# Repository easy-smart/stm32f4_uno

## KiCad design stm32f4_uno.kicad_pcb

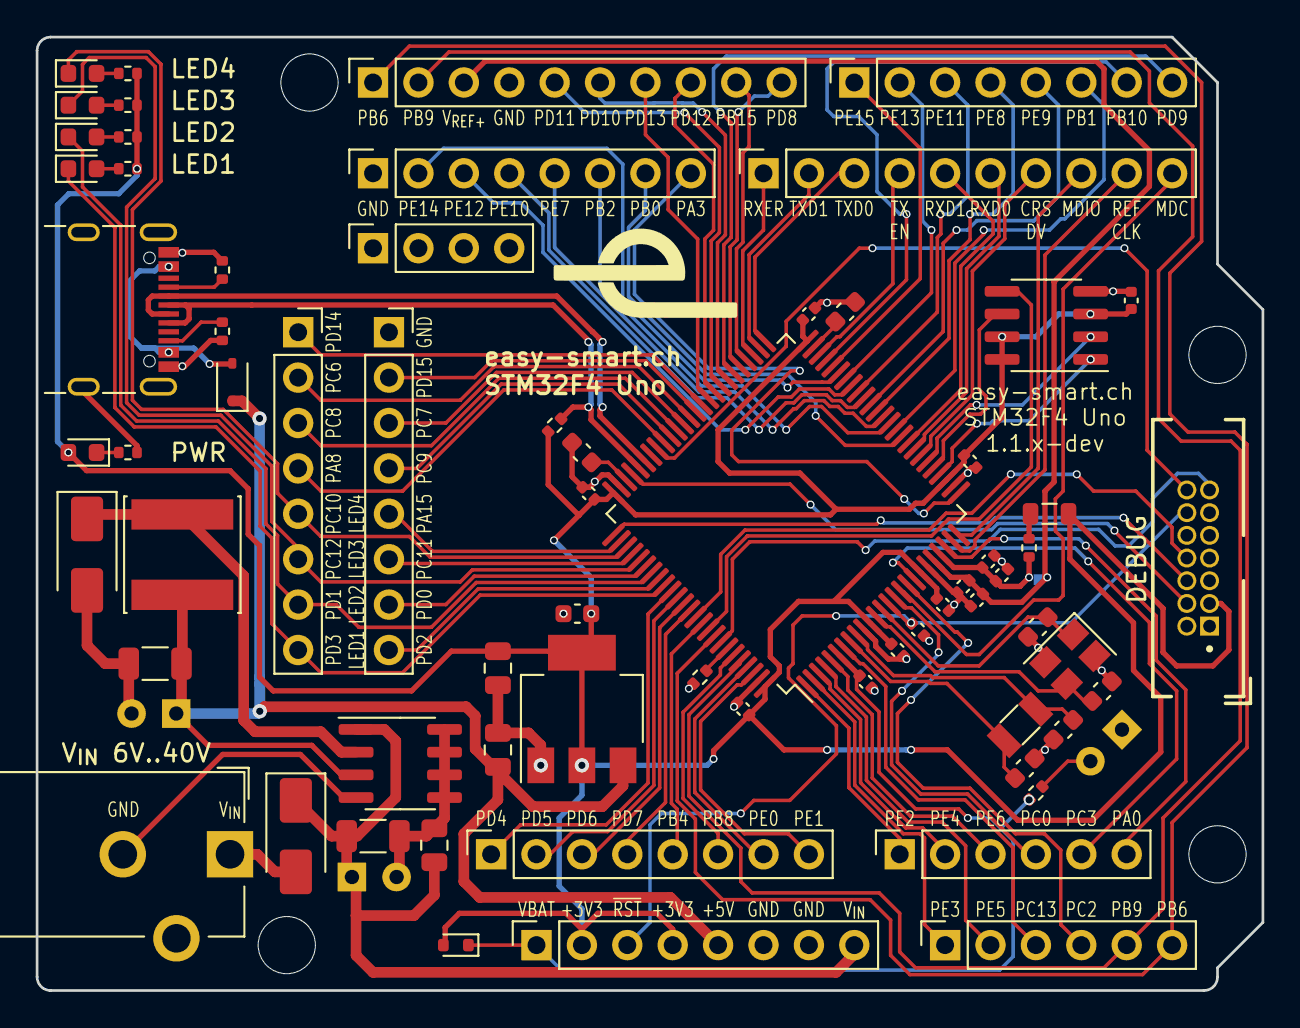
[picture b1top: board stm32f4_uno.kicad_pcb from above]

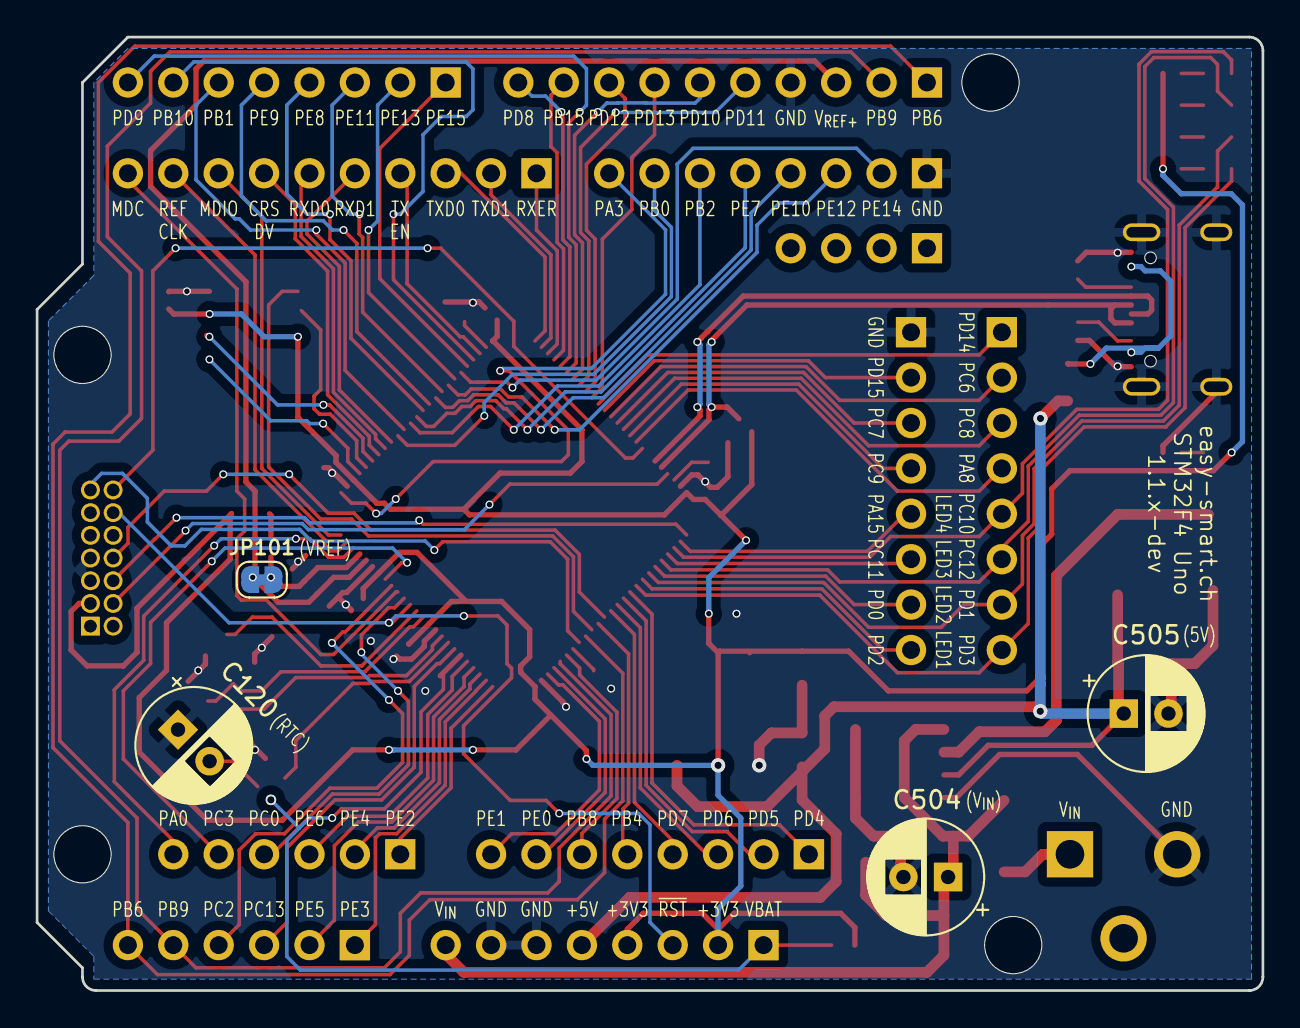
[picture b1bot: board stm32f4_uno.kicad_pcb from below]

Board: 2 copper layers, 68.6 x 53.3 mm, 75 parts (4 on the bottom side), 104 nets.

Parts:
C101: 4u7 16V; C_0603_1608Metric
C102, C103, C104, C105, C106, C107, C108, C110: 100n; C_0402_1005Metric
C109, C111, C112: 1u; C_0402_1005Metric
C113, C301: 100n 16V; C_0402_1005Metric
C114, C115: 30p 50V; C_0603_1608Metric
C116, C117: 2u2 16V; C_0603_1608Metric
C118, C119: 8p2 50V; C_0603_1608Metric
C120, C504, C505: ?; CP_Radial_D6.3mm_P2.50mm
C401, C402: 22u 25V; C_0805_2012Metric
C501: 1u 50V; C_0805_2012Metric
C502: 10u 50V; C_1206_3216Metric
C503: 47uF 10V; C_1206_3216Metric
D101: LED green; LED_0603_1608Metric
D102: LED yellow; LED_0603_1608Metric
D103: LED red; LED_0603_1608Metric
D104: LED blue; LED_0603_1608Metric
D105: 1N5819WS; D_SOD-323
D106: SS210; D_SMA
D107: 1N4148WT; D_SOD-523
D401: LED green (PWR); LED_0603_1608Metric
D501: SS34; D_SMA
J1: Conn_ST_STDC14; Amphenol ICC 20021511-00014T4LF
J101, J103, J104, J105: STM32 GPIO; PinSocket_1x08_P2.54mm_Vertical
J102: Digital/PWM; PinSocket_1x10_P2.54mm_Vertical
J106: Power; PinSocket_1x08_P2.54mm_Vertical
J107: Ethernet; PinSocket_1x10_P2.54mm_Vertical
J108: STM32 GPIO; PinSocket_1x06_P2.54mm_Vertical
J109: Digital/PWM; PinSocket_1x08_P2.54mm_Vertical
J110: Analog; PinSocket_1x06_P2.54mm_Vertical
J111: Conn_01x04; PinSocket_1x04_P2.54mm_Vertical
J112: Barrel_Jack; CUI Devices PJ-102AH.pdf
J201: SHOU HAN TYPE-C 16PIN 2MD(073) (C2765186); SHOU HAN TYPE-C 16PIN 2MD(073)
JP101: Jumper_2_Bridged; SolderJumper-2_P1.3mm_Bridged_RoundedPad1.0x1.5mm
L101: 600Ω@100MHz; L_0805_2012Metric
L501: 68uH 1A; L_Sunlord_SWPA6045S
MH1, MH2, MH3, MH4: MountingHole_3.2mm
R101: 47; R_0402_1005Metric
R102: 10k; R_0402_1005Metric
R103, R401: 200; R_0402_1005Metric
R104, R105: 330; R_0402_1005Metric
R106: 150; R_0402_1005Metric
R107: 100; R_0402_1005Metric
R201, R202: 5k1; R_0402_1005Metric
R203: 1k5; R_0402_1005Metric
U101: STM32F407VGT6; LQFP-100_14x14mm_P0.5mm
U301: SST26VF016BEUI-104I/SN; SOIC-8_3.9x4.9mm_P1.27mm
U401: AMS1117-3.3; SOT-223-3_TabPin2
U501: XL1509-5.0; SOIC-8_3.9x4.9mm_P1.27mm
Y101: 25MHz; Crystal_SMD_3225-4Pin_3.2x2.5mm
Y102: 32.768kHz; Crystal_SMD_3215-2Pin_3.2x1.5mm

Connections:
+3V3: C101.1, C102.1, C103.1, C104.1, C105.1, C106.1, C107.1, C301.2, C402.1, D107.2 (A), D401.2 (A), J1.3 (VCC), J106.2, J106.4, L101.2, R103.2, R104.2, R105.2, R106.2, R203.1, U101.11 (VDD), U101.19 (VDD), U101.28 (VDD), U101.50 (VDD), U101.75 (VDD), U101.100 (VDD), U301.3 (~WP), U301.7 (~HOLD), U301.8 (VDD), U401.2 (VO)
+5V: C401.1, C503.1, C505.1, D105.1 (K), J106.5, L501.1, U401.3 (VI), U501.3 (FB)
/40V->5V/VOUT: D501.1 (K), L501.2, U501.2 (OUT)
/BOOT0: R102.1, U101.94 (BOOT0)
/CAP_1: C116.1, U101.49 (VCAP_1)
/CAP_2: C117.1, U101.73 (VCAP_2)
/ETH_CRS_DV: J107.7, U101.32 (PA7)
/ETH_MDC: J107.10, U101.16 (PC1)
/ETH_MDIO: J107.8, U101.25 (PA2)
/ETH_REF_CLK: J107.9, U101.24 (PA1)
/ETH_RXD0: J107.6, U101.33 (PC4)
/ETH_RXD1: J107.5, U101.34 (PC5)
/ETH_RXER: J107.1, U101.53 (PB14)
/ETH_TXD0: J107.3, U101.51 (PB12)
/ETH_TXD1: J107.2, U101.52 (PB13)
/ETH_TX_EN: J107.4, U101.48 (PB11)
/HSE_IN: C114.1, U101.12 (PH0), Y101.3
/HSE_OUT: C115.1, U101.13 (PH1), Y101.1
/LSE_IN: C118.2, U101.8 (PC14), Y102.2
/LSE_OUT: C119.2, U101.9 (PC15), Y102.1
/PA0: J108.6, U101.23 (PA0)
/PA3: J104.8, U101.26 (PA3)
/PA8: J101.4, U101.67 (PA8)
/PA15: J103.5, U101.77 (PA15)
/PB0: J104.7, U101.35 (PB0)
/PB1: J109.6, U101.36 (PB1)
/PB2: J104.6, U101.37 (PB2)
/PB4: J105.5, U101.90 (PB4)
/PB6: J102.1, J110.6, U101.92 (PB6)
/PB8: J105.6, U101.95 (PB8)
/PB9: J102.2, J110.5, U101.96 (PB9)
/PB10: J109.7, U101.47 (PB10)
/PB15: J102.9, U101.54 (PB15)
/PC0: J108.4, U101.15 (PC0)
/PC2: J110.4, U101.17 (PC2)
/PC3: J108.5, U101.18 (PC3)
/PC6: J101.2, U101.63 (PC6)
/PC7: J103.3, U101.64 (PC7)
/PC8: J101.3, U101.65 (PC8)
/PC9: J103.4, U101.66 (PC9)
/PC10/LED4_BLU: D104.1 (K), J101.5, U101.78 (PC10)
/PC11: J103.6, U101.79 (PC11)
/PC12/LED3_RED: D103.1 (K), J101.6, U101.80 (PC12)
/PC13: J110.3, U101.7 (PC13)
/PD0: J103.7, U101.81 (PD0)
/PD1/LED2_ORG: D102.1 (K), J101.7, U101.82 (PD1)
/PD2: J103.8, U101.83 (PD2)
/PD3/LED1_GRN: D101.1 (K), J101.8, U101.84 (PD3)
/PD4: J105.1, U101.85 (PD4)
/PD5: J105.2, U101.86 (PD5)
/PD6: J105.3, U101.87 (PD6)
/PD7: J105.4, U101.88 (PD7)
/PD8: J102.10, U101.55 (PD8)
/PD9: J109.8, U101.56 (PD9)
/PD10: J102.6, U101.57 (PD10)
/PD11: J102.5, U101.58 (PD11)
/PD12: J102.8, U101.59 (PD12)
/PD13: J102.7, U101.60 (PD13)
/PD14: J101.1, U101.61 (PD14)
/PD15: J103.2, U101.62 (PD15)
/PE0: J105.7, U101.97 (PE0)
/PE1: J105.8, U101.98 (PE1)
/PE2: J108.1, U101.1 (PE2)
/PE3: J110.1, U101.2 (PE3)
/PE4: J108.2, U101.3 (PE4)
/PE5: J110.2, U101.4 (PE5)
/PE6: J108.3, U101.5 (PE6)
/PE7: J104.5, U101.38 (PE7)
/PE8: J109.4, U101.39 (PE8)
/PE9: J109.5, U101.40 (PE9)
/PE10: J104.4, U101.41 (PE10)
/PE11: J109.3, U101.42 (PE11)
/PE12: J104.3, U101.43 (PE12)
/PE13: J109.2, U101.44 (PE13)
/PE14: J104.2, U101.45 (PE14)
/PE15: J109.1, U101.46 (PE15)
/SPI1_MISO: U101.31 (PA6), U301.2 (SO)
/SPI1_MOSI: U101.91 (PB5), U301.5 (SI)
/SPI1_NSS: U101.29 (PA4), U301.1 (~CE)
/SPI1_SCK: U101.30 (PA5), U301.6 (SCK)
/SYS_SWCLK: J1.6 (JCLK/SWCLK), U101.76 (PA14)
/SYS_SWDIO: J1.4 (JTMS/SWDIO), U101.72 (PA13)
/SYS_SWO: J1.8 (JTDO/SWO), U101.89 (PB3)
/USART1_RX: J1.13 (VCP_RX), U101.93 (PB7)
/USART1_TX: J1.14 (VCP_TX), U101.68 (PA9)
/USB/CC1: J201.A5 (CC1), R201.2
/USB/CC2: J201.B5 (CC2), R202.2
/USB_OTG_FS_D+: J201.A6 (D+), J201.B6 (D+), R203.2, U101.71 (PA12)
/USB_OTG_FS_D-: J201.A7 (D-), J201.B7 (D-), U101.70 (PA11)
/VBAT: C112.1, D107.1 (K), J106.1, R107.2, U101.6 (VBAT)
/VBUS: D105.2 (A), J201.A4 (VBUS), J201.A9 (VBUS), J201.B4 (VBUS), J201.B9 (VBUS)
/VDDA: C110.1, C111.1, JP101.2 (B), R101.2, U101.22 (VDDA)
/VREF+: C108.1, C109.1, J102.3, JP101.1 (A), U101.21 (VREF+)
/V_{IN}: C501.1, C502.1, C504.1, D106.1 (K), J106.8, U501.1 (VIN)
/~RESET: C113.1, J1.12 (~RST), J106.3, U101.14 (NRST)
GND: C101.2, C102.2, C103.2, C104.2, C105.2, C106.2, C107.2, C108.2, C109.2, C110.2, C111.2, C112.2, C113.2, C114.2, C115.2, C116.2, C117.2, C118.1, C119.1, C120.1, C301.1, C401.2, C402.2, C501.2, C502.2, C503.2, C504.2, C505.2, D501.2 (A), J1.5 (GND), J1.7 (GND), J102.4, J103.1, J104.1, J106.6, J106.7, J112.2, J201.A1 (GND), J201.A12 (GND), J201.B1 (GND), J201.B12 (GND), J201.S1 (SHIELD), R102.2, R201.1, R202.1, R401.1, U101.10 (VSS), U101.20 (VSSA), U101.27 (VSS), U101.74 (VSS), U101.99 (VSS), U301.4 (VSS), U401.1 (GND), U501.4 (~EN), U501.5 (GND), U501.6 (GND), U501.7 (GND), U501.8 (GND), Y101.2, Y101.4
unnamed: C120.2, R107.1
unnamed: D101.2 (A), R103.1
unnamed: D102.2 (A), R104.1
unnamed: D103.2 (A), R105.1
unnamed: D104.2 (A), R106.1
unnamed: D106.2 (A), J112.1
unnamed: D401.1 (K), R401.2
unnamed: L101.1, R101.1

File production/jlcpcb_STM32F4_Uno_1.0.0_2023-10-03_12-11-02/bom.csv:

Designator,Footprint,Quantity,Value,LCSC Part #
C101,0603,1,4u7 16V,C19666
"C102, C103, C104, C105, C106, C107, C108, C110",0402,8,100n,C1525
"C109, C111, C112",0402,3,1u,C52923
"C113, C301",0402,2,100n 16V,C1525
"C114, C115",0603,2,30p 50V,C1658
"C116, C117",0603,2,2u2 16V,C23630
"C118, C119",0603,2,8p2 50V,C1685
"C401, C402",0805,2,22u 25V,C45783
C501,0805,1,1u 50V,C28323
C502,1206,1,10u 50V,C13585
C503,1206,1,47uF 10V,C96123
D101,0603,1,LED green,C72043
D102,0603,1,LED yellow,C72038
D103,0603,1,LED red,C2286
D104,0603,1,LED blue,C72041
D105,D_SOD-323,1,1N5819WS,C191023
D106,D_SMA,1,SS210,C14996
D401,0603,1,LED green (PWR),C72043
D501,D_SMA,1,SS34,C8678
J201,SHOU HAN TYPE-C 16PIN 2MD(073),1,SHOU HAN TYPE-C 16PIN 2MD(073) (C2765186),C2765186
L101,0805,1,600Ω@100MHz,C1017
L501,L_Sunlord_SWPA6045S,1,68uH 1A,C142105
R101,0402,1,47,C25118
R102,0402,1,10k,C25744
"R103, R401",0402,2,200,C25087
"R104, R105",0402,2,330,C25104
R106,0402,1,150,C25082
"R201, R202",0402,2,5k1,C25905
R203,0402,1,1k5,C25867
U101,LQFP-100_14x14mm_P0.5mm,1,STM32F407VGT6,C12345
U401,SOT-223-3_TabPin2,1,AMS1117-3.3,C6186
U501,SOIC-8_3.9x4.9mm_P1.27mm,1,XL1509-5.0,C61063
Y101,Crystal_SMD_3225-4Pin_3.2x2.5mm,1,25MHz,C9006
Y102,Crystal_SMD_3215-2Pin_3.2x1.5mm,1,32.768kHz,C95361

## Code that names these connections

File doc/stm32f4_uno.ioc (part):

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Mcu.Name=STM32F407V(E-G)Tx
Mcu.Package=LQFP100
Mcu.UserName=STM32F407VGTx
PA0-WKUP.GPIOParameters=GPIO_Label
PA0-WKUP.GPIO_Label=J108_6
PA0-WKUP.Signal=GPIO_Analog
PA1.Mode=RMII
PA1.Signal=ETH_REF_CLK
PA10.Mode=OTG/Dual_Role_Device
PA10.Signal=USB_OTG_FS_ID
PA11.Mode=OTG/Dual_Role_Device
PA11.Signal=USB_OTG_FS_DM
PA12.Mode=OTG/Dual_Role_Device
PA12.Signal=USB_OTG_FS_DP
PA13.Mode=Trace_Asynchronous_SW
PA13.Signal=SYS_JTMS-SWDIO
PA14.Mode=Trace_Asynchronous_SW
PA14.Signal=SYS_JTCK-SWCLK
PA15.GPIOParameters=GPIO_Label
PA15.GPIO_Label=J111_5
PA15.Signal=GPIO_Analog
PA2.Mode=RMII
PA2.Signal=ETH_MDIO
PA3.GPIOParameters=GPIO_Label
PA3.GPIO_Label=J107_8
PA3.Signal=GPIO_Output
PA4.Mode=NSS_Signal_Hard_Output
PA4.Signal=SPI1_NSS
PA5.Mode=Full_Duplex_Master
PA5.Signal=SPI1_SCK
PA6.Mode=Full_Duplex_Master
PA6.Signal=SPI1_MISO
PA7.Mode=RMII
PA7.Signal=ETH_CRS_DV
PA8.GPIOParameters=GPIO_Label
PA8.GPIO_Label=J110_4
PA8.Signal=GPIO_Analog
PA9.Mode=Asynchronous
PA9.Signal=USART1_TX
PB0.GPIOParameters=GPIO_Label
PB0.GPIO_Label=J107_7
PB0.Signal=GPIO_Output
PB1.GPIOParameters=GPIO_Label
PB1.GPIO_Label=D2
PB1.Signal=GPIO_Output
PB10.GPIOParameters=GPIO_Label
PB10.GPIO_Label=USART3_TX/D0
PB10.Mode=Asynchronous
PB10.Signal=USART3_TX
PB11.Mode=RMII
PB11.Signal=ETH_TX_EN
PB12.Mode=RMII
PB12.Signal=ETH_TXD0
PB13.Mode=RMII
PB13.Signal=ETH_TXD1
PB14.GPIOParameters=GPIO_Label
PB14.GPIO_Label=ETH_RXER
PB14.Signal=GPIO_Input
PB15.GPIOParameters=GPIO_Label
PB15.GPIO_Label=D9*
PB15.Signal=S_TIM12_CH2
PB2.GPIOParameters=GPIO_Label
PB2.GPIO_Label=J107_6
PB2.Signal=GPIO_Output
PB3.Mode=Trace_Asynchronous_SW
PB3.Signal=SYS_JTDO-SWO
PB4.GPIOParameters=GPIO_Label
PB4.GPIO_Label=J109_5
PB4.Signal=GPIO_Analog
PB5.Mode=Full_Duplex_Master
PB5.Signal=SPI1_MOSI
PB6.Mode=I2C
PB6.Signal=I2C1_SCL
PB7.Mode=Asynchronous
PB7.Signal=USART1_RX
PB8.GPIOParameters=GPIO_Label
PB8.GPIO_Label=J109_6
PB8.Signal=GPIO_Output
PB9.Mode=I2C
PB9.Signal=I2C1_SDA
PC0.GPIOParameters=GPIO_Label
PC0.GPIO_Label=J108_4
PC0.Signal=GPIO_Analog
PC1.Mode=RMII
PC1.Signal=ETH_MDC
PC10.GPIOParameters=GPIO_Label
PC10.GPIO_Label=J110_5/LED4_BLU
PC10.Signal=GPIO_Analog
PC11.GPIOParameters=GPIO_Label
PC11.GPIO_Label=J111_6
PC11.Signal=GPIO_Analog
PC12.GPIOParameters=GPIO_Label
PC12.GPIO_Label=J110_6/LED3_RED
PC12.Signal=GPIO_Analog
PC13-ANTI_TAMP.GPIOParameters=GPIO_Label
PC13-ANTI_TAMP.GPIO_Label=A2
PC13-ANTI_TAMP.Signal=GPIO_Analog
PC14-OSC32_IN.Mode=LSE-External-Oscillator
PC14-OSC32_IN.Signal=RCC_OSC32_IN
PC15-OSC32_OUT.Mode=LSE-External-Oscillator
PC15-OSC32_OUT.Signal=RCC_OSC32_OUT
PC2.GPIOParameters=GPIO_Label
PC2.GPIO_Label=A3
PC2.Signal=GPIO_Analog
PC3.GPIOParameters=GPIO_Label
PC3.GPIO_Label=J108_5
PC3.Signal=GPIO_Analog
PC4.Mode=RMII
PC4.Signal=ETH_RXD0
PC5.Mode=RMII
PC5.Signal=ETH_RXD1
PC6.GPIOParameters=GPIO_Label
PC6.GPIO_Label=J110_2
PC6.Signal=GPIO_Analog
PC7.GPIOParameters=GPIO_Label
PC7.GPIO_Label=J111_3
PC7.Signal=GPIO_Analog
PC8.GPIOParameters=GPIO_Label
PC8.GPIO_Label=J110_3
PC8.Signal=GPIO_Analog
PC9.GPIOParameters=GPIO_Label
PC9.GPIO_Label=J111_4
PC9.Signal=GPIO_Analog
PD0.GPIOParameters=GPIO_Label
PD0.GPIO_Label=J111_7
PD0.Signal=GPIO_Analog
PD1.GPIOParameters=GPIO_Label
PD1.GPIO_Label=J110_7/LED2_ORG
PD1.Signal=GPIO_Analog
PD10.GPIOParameters=GPIO_Label
PD10.GPIO_Label=D12
PD10.Signal=GPIO_Output
PD11.GPIOParameters=GPIO_Label
PD11.GPIO_Label=D13
PD11.Signal=GPIO_Output
PD12.GPIOParameters=GPIO_Label
PD12.GPIO_Label=D10*
PD12.Signal=S_TIM4_CH1
PD13.GPIOParameters=GPIO_Label
PD13.GPIO_Label=D11*
PD13.Signal=S_TIM4_CH2
PD14.GPIOParameters=GPIO_Label
PD14.GPIO_Label=J110_1
PD14.Signal=GPIO_Analog
PD15.GPIOParameters=GPIO_Label
PD15.GPIO_Label=J111_2
PD15.Signal=GPIO_Analog
PD2.GPIOParameters=GPIO_Label
PD2.GPIO_Label=J111_8
PD2.Signal=GPIO_Analog
PD3.GPIOParameters=GPIO_Label
PD3.GPIO_Label=J110_8/LED1_GRN
PD3.Signal=GPIO_Analog
PD4.GPIOParameters=GPIO_Label
PD4.GPIO_Label=J109_1
PD4.Signal=GPIO_Analog
PD5.GPIOParameters=GPIO_Label
PD5.GPIO_Label=J109_2
PD5.Signal=GPIO_Analog
PD6.GPIOParameters=GPIO_Label
PD6.GPIO_Label=J109_3
PD6.Signal=GPIO_Analog
PD7.GPIOParameters=GPIO_Label
PD7.GPIO_Label=J109_4
PD7.Signal=GPIO_Analog
PD8.GPIOParameters=GPIO_Label
PD8.GPIO_Label=D8
PD8.Signal=GPIO_Output
PD9.GPIOParameters=GPIO_Label
PD9.GPIO_Label=USART3_RX/D0
PD9.Mode=Asynchronous
PD9.Signal=USART3_RX
PE0.GPIOParameters=GPIO_Label
PE0.GPIO_Label=J109_7
PE0.Signal=GPIO_Analog
PE1.GPIOParameters=GPIO_Label
PE1.GPIO_Label=J109_8
PE1.Signal=GPIO_Analog
PE10.GPIOParameters=GPIO_Label
PE10.GPIO_Label=J107_4
PE10.Signal=GPIO_Output
PE11.GPIOParameters=GPIO_Label
PE11.GPIO_Label=D5*
PE11.Signal=S_TIM1_CH2
PE12.GPIOParameters=GPIO_Label
PE12.GPIO_Label=J107_3
PE12.Signal=GPIO_Output
PE13.GPIOParameters=GPIO_Label
PE13.GPIO_Label=D6*
PE13.Signal=S_TIM1_CH3
PE14.GPIOParameters=GPIO_Label
PE14.GPIO_Label=J107_2
PE14.Signal=GPIO_Output
PE15.GPIOParameters=GPIO_Label
PE15.GPIO_Label=D7
PE15.Signal=GPIO_Output
PE2.GPIOParameters=GPIO_Label
PE2.GPIO_Label=J108_1
PE2.Signal=GPIO_Analog
PE3.GPIOParameters=GPIO_Label
PE3.GPIO_Label=A0
PE3.Signal=GPIO_Analog
PE4.GPIOParameters=GPIO_Label
PE4.GPIO_Label=J108_2
PE4.Signal=GPIO_Analog
PE5.GPIOParameters=GPIO_Label
PE5.GPIO_Label=A1
PE5.Signal=GPIO_Analog
PE6.GPIOParameters=GPIO_Label
PE6.GPIO_Label=J108_3
PE6.Signal=GPIO_Analog
PE7.GPIOParameters=GPIO_Label
PE7.GPIO_Label=J107_5
PE7.Signal=GPIO_Output
PE8.GPIOParameters=GPIO_Label
PE8.GPIO_Label=D4
PE8.Signal=GPIO_Output
PE9.GPIOParameters=GPIO_Label
PE9.GPIO_Label=D3*
PE9.Signal=S_TIM1_CH1
PH0-OSC_IN.Mode=HSE-External-Oscillator
PH0-OSC_IN.Signal=RCC_OSC_IN
PH1-OSC_OUT.Mode=HSE-External-Oscillator
PH1-OSC_OUT.Signal=RCC_OSC_OUT
RCC.HSE_VALUE=25000000
RCC.SYSCLKFreq_VALUE=168000000
RCC.SYSCLKSource=RCC_SYSCLKSOURCE_PLLCLK
board=custom

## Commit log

2023-09-08 Finish schematic
2023-09-08 Finish schematic with all pins
2023-09-11 First version done
2023-09-14 Add ETH_RXER
2023-09-14 Replace 3V3 LDO for a 1A model
2023-09-14 Set DNP on devices not to populate
2023-09-20 #1 Use new central library KiCad-Lib
2023-09-20 Add CUI Devices PJ-102AH 3D model and export PCB 3D model
2023-09-23 Replaced 5V LDO for a 40V->5V buck converter
2023-09-24 Lock pin sockets
2023-10-01 Feature/40 v ps (#3)
    * WIP
    * WIP
    * Replaced 5V LDO for a 40V->5V buck converter
    * Lock pin sockets
2023-10-01 #2 Add silkscreen texts
2023-10-02 #4 Match pcb to ethernet and poe
2023-10-03 Release 1.0.0 sent to JLCPCB
2023-10-03 PCB production confirmed
2023-10-11 #5 Add blinktest
2023-10-11 #6 Add swotest
2023-10-12 #7 Implement usbtest
2023-10-12 #8 Implement flasheuitest
2023-10-13 #9 Implement ethtest
2023-10-14 Add product photos
2023-10-14 Add measurement of the 40V to 5V converter
2023-10-17 Change version and add workflow
2023-10-17 Move text
2024-02-23 Add product pictures
2024-11-11 #10 Wrong text on pin 3 (J102)
2024-11-11 #13 USART1 has alternative wiring (PB7, not PA10)
2024-11-11 #15 Add all pin sockets
2024-11-11 #14 Add optional capacitor for RTC operation
2024-11-28 #16 Silkscreen texts
